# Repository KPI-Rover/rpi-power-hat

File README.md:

# RPI Power HAT

**In development! Not verified!**

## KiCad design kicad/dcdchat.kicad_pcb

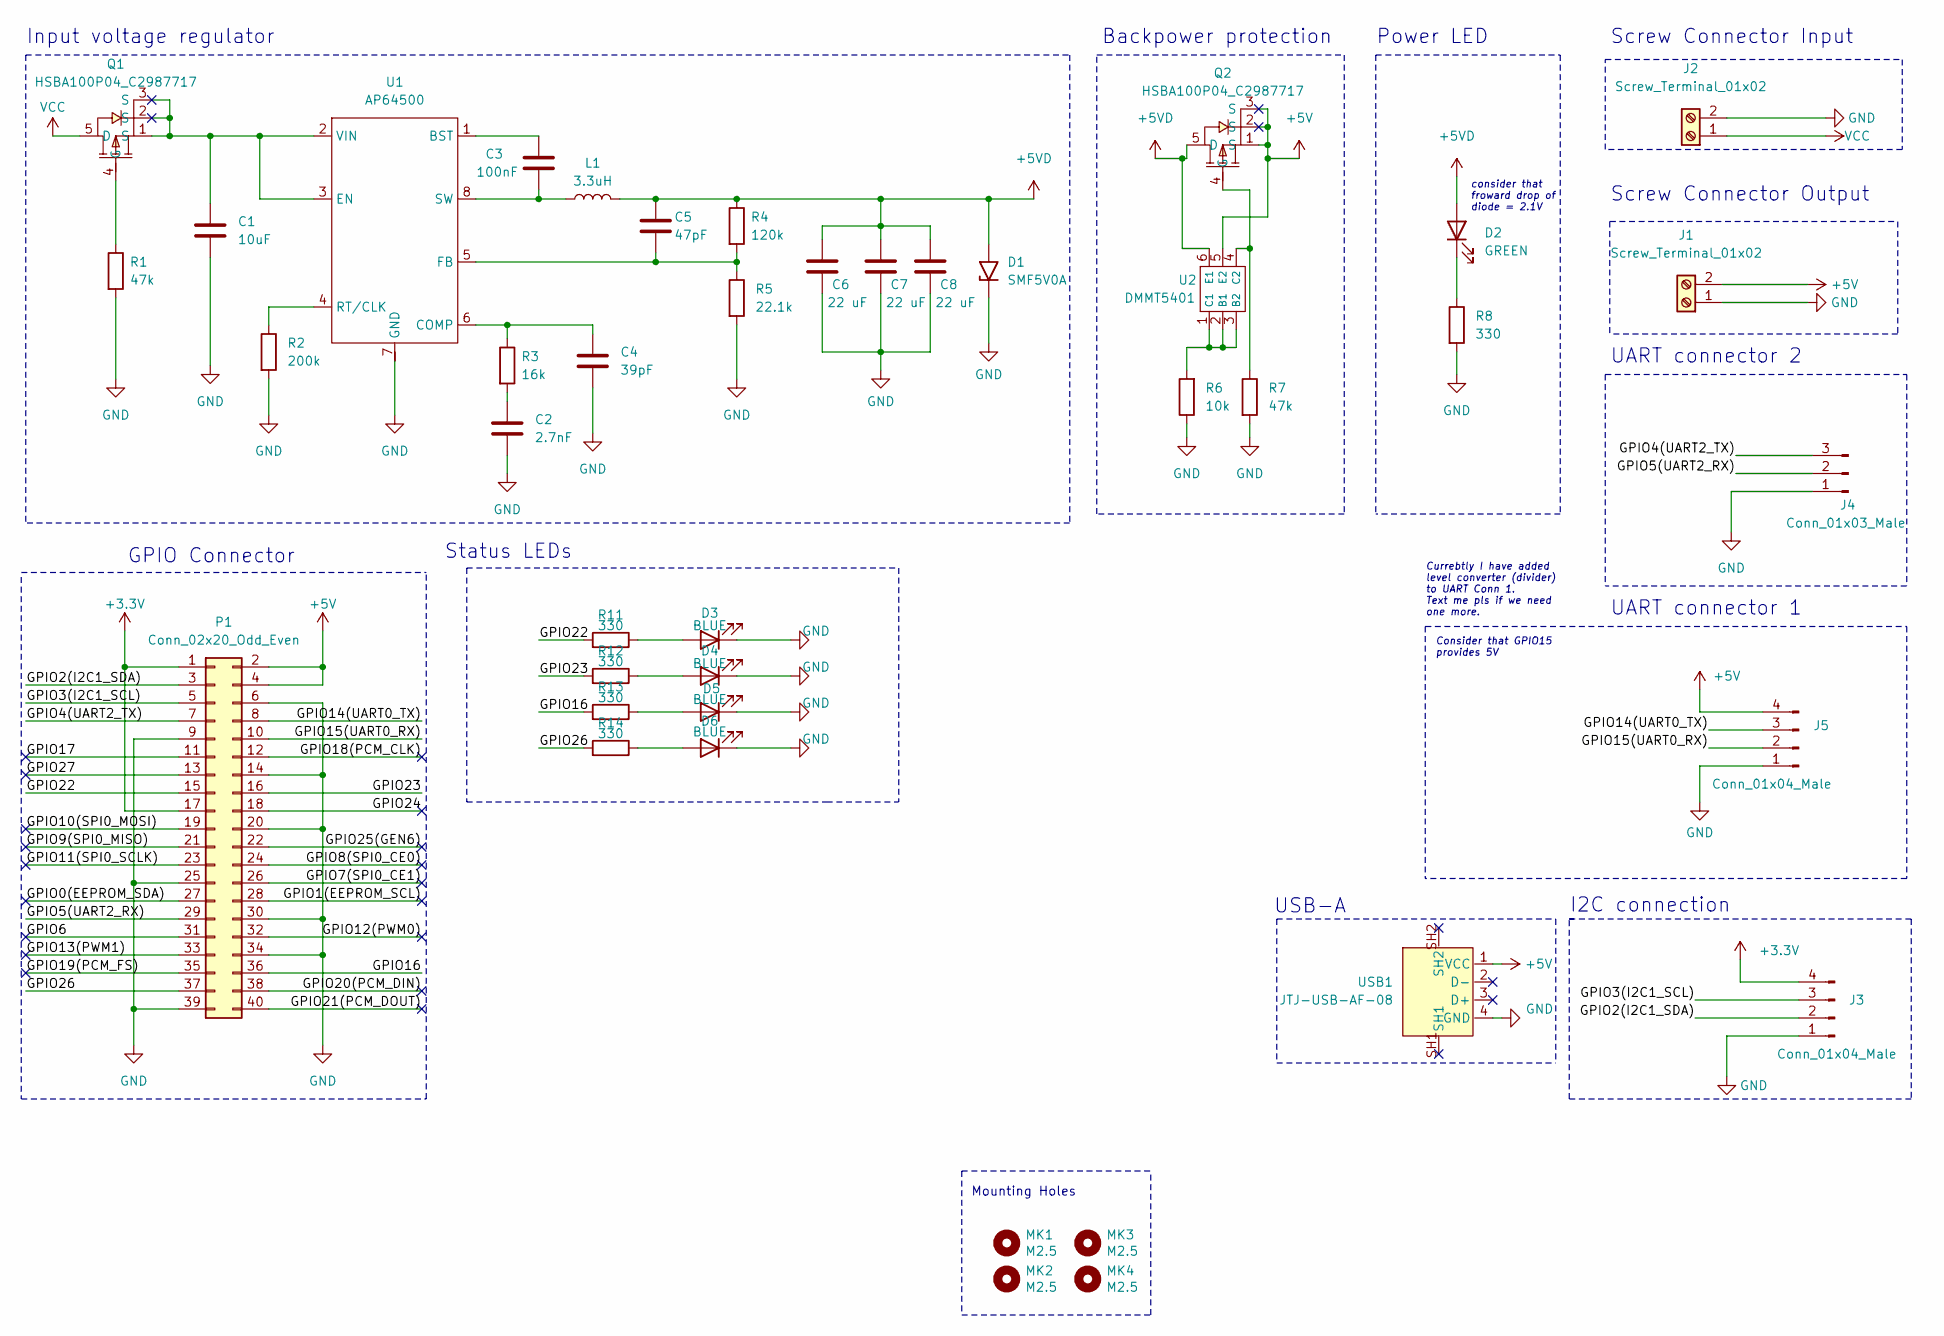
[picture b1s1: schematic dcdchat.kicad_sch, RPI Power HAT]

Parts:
C1: 10uF; C_1206_3216Metric; LCSC C13585
C2: 2.7nF; C_0805_2012Metric; LCSC C2918070
C3: 100nF; C_0805_2012Metric; LCSC C28233
C4: 39pF; C_0805_2012Metric; LCSC C576897
C5: 47pF; C_0805_2012Metric; LCSC C113821
C6, C7, C8: 22 uF; C_1206_3216Metric; LCSC C87996
D1: SMF5V0A; D_SMF; LCSC C42387343
D2: GREEN; LED_0805_2012Metric; LCSC C5875740
D3, D4, D5, D6: BLUE; LED_0805_2012Metric; LCSC C965817
J1, J2: Screw_Terminal_01x02; CONN-TH_2P-P5.08; LCSC C3018698
J3, J5: Conn_01x04_Male; JST_PH_B4B-PH-K_1x04_P2.00mm_Vertical; LCSC C131334
J4: Conn_01x03_Male; JST_PH_B3B-PH-K_1x03_P2.00mm_Vertical; LCSC C131339
L1: 3.3uH; IND-SMD_L11.6-W10.1; LCSC C7587741
MK1, MK2, MK3, MK4: M2.5; MountingHole_2.7mm_M2.5_Pad
P1: Conn_02x20_Odd_Even; PinSocket_2x20_P2.54mm_Vertical; Manufacturer_Part_Number C50982; LCSC C50982
Q1, Q2: HSBA100P04_C2987717; DFN-8_L5.7-W5.1-P1.27-LS6.1-BL-1; LCSC Part C2987717
R1, R7: 47k; R_0805_2012Metric; LCSC C2989281
R2: 200k; R_0805_2012Metric; LCSC C728645
R3: 16k; R_0805_2012Metric; LCSC C865809
R4: 120k; R_0805_2012Metric; LCSC C103948
R5: 22.1k; R_0805_2012Metric; LCSC C2692772
R6: 10k; R_0805_2012Metric; LCSC C110775
R8, R11, R12, R13, R14: 330; R_0805_2012Metric; LCSC C2989109
U1: AP64500; AP64500SP-13; LCSC C2070920
U2: DMMT5401; SOT-23-6; LCSC C154733
USB1: JTJ-USB-AF-08; USB-A-TH__USB-AF-90; LCSC Part C2345

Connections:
+3.3V: J3.4, P1.1, P1.17
+5V: J1.2, J5.4, P1.2, P1.4, Q2.1 (S), Q2.2 (S), Q2.3 (S), U2.5 (E2), USB1.1 (VCC)
+5VD: C5.1, C6.1, C7.1, C8.1, D1.2 (A2), D2.2 (A), L1.2, Q2.5 (D), R4.1, U2.6 (E1)
/GPIO0(EEPROM_SDA): P1.27
/GPIO1(EEPROM_SCL): P1.28
/GPIO2(I2C1_SDA): J3.2, P1.3
/GPIO3(I2C1_SCL): J3.3, P1.5
/GPIO4(UART2_TX): J4.3, P1.7
/GPIO5(UART2_RX): J4.2, P1.29
/GPIO6: P1.31
/GPIO7(SPI0_CE1): P1.26
/GPIO8(SPI0_CE0): P1.24
/GPIO9(SPI0_MISO): P1.21
/GPIO10(SPI0_MOSI): P1.19
/GPIO11(SPI0_SCLK): P1.23
/GPIO12(PWM0): P1.32
/GPIO13(PWM1): P1.33
/GPIO14(UART0_TX): J5.3, P1.8
/GPIO15(UART0_RX): J5.2, P1.10
/GPIO16: P1.36, R13.2
/GPIO17: P1.11
/GPIO18(PCM_CLK): P1.12
/GPIO19(PCM_FS): P1.35
/GPIO20(PCM_DIN): P1.38
/GPIO21(PCM_DOUT): P1.40
/GPIO22: P1.15, R11.2
/GPIO23: P1.16, R12.2
/GPIO24: P1.18
/GPIO25(GEN6): P1.22
/GPIO26: P1.37, R14.2
/GPIO27: P1.13
GND: C1.2, C2.2, C4.2, C6.2, C7.2, C8.2, D1.1 (A1), D3.1 (K), D4.1 (K), D5.1 (K), D6.1 (K), J1.1, J2.2, J3.1, J4.1, J5.1, P1.6, P1.9, P1.14, P1.20, P1.25, P1.30, P1.34, P1.39, R1.2, R2.2, R5.2, R6.1, R7.2, R8.2, U1.7 (GND), U1.EPAD, USB1.4 (GND)
unnamed: C2.1, R3.2
unnamed: D2.1 (K), R8.1
unnamed: D3.2 (A), R11.1
unnamed: D4.2 (A), R12.1
unnamed: D5.2 (A), R13.1
unnamed: D6.2 (A), R14.1
unnamed: Q1.4 (G), R1.1
unnamed: Q2.4 (G), R7.1, U2.4 (C2)
unnamed: C3.1, U1.1 (BST)
unnamed: C4.1, R3.1, U1.6 (COMP)
unnamed: C5.2, R4.2, R5.1, U1.5 (FB)
unnamed: R2.1, U1.4 (RT/CLK)
unnamed: C3.2, L1.1, U1.8 (SW)
unnamed: R6.2, U2.1 (C1), U2.2 (B1), U2.3 (B2)
VCC: J2.1, Q1.5 (D)

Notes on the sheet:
USB-A
Currebtly I have added level converter (divider) to UART Conn 1. Text me pls if we need one more.
Backpower protection
Mounting Holes
I2C connection
GPIO Connector
UART connector 2
Status LEDs
Consider that GPIO15 provides 5V
consider that froward drop of diode = 2.1V
Screw Connector Output
Input voltage regulator
UART connector 1
Power LED
Screw Connector Input

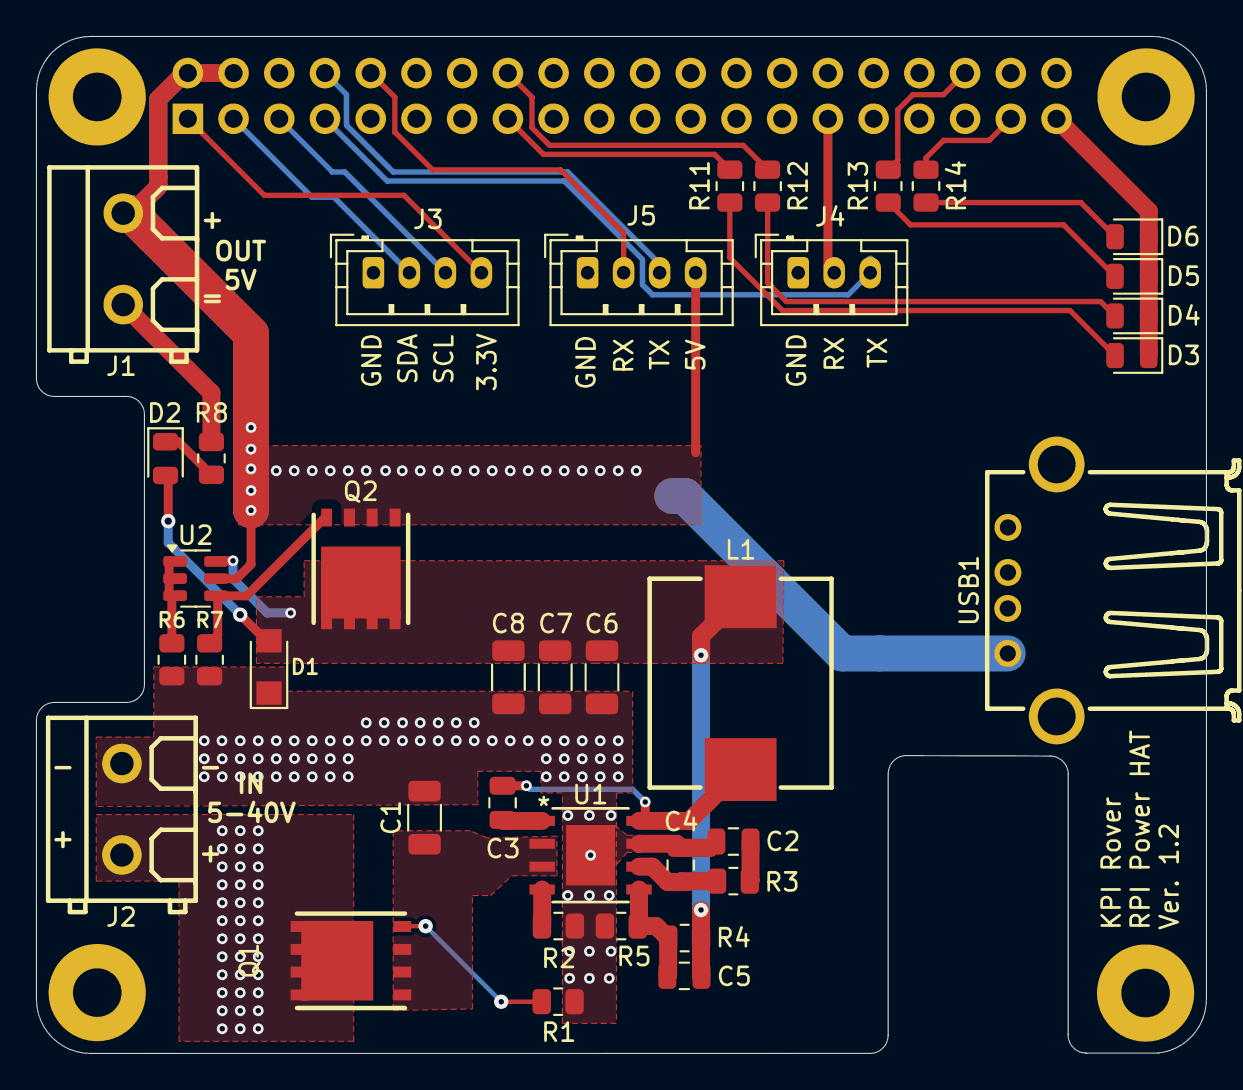
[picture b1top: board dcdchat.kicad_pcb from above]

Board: 2 copper layers, 65.0 x 56.5 mm, 42 parts (1 on the bottom side), 29 nets.

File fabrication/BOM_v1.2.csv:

Reference,Value,Qty,LCSC,LCSC Part
C1,10uF,1,C13585 ,
C2,2.7nF,1,C2918070,
C3,100nF,1,C28233,
C4,39pF,1,C576897,
C5,47pF,1,C113821,
"C6,C7,C8",22 uF,3,C87996,
D1,SMF5V0A,1,C42387343,
D2,GREEN,1,C5875740,
"D3,D4,D5,D6",BLUE,4,C965817,
"J1,J2",Screw_Terminal_01x02,2,C3018698,
"J3,J5",Conn_01x04_Male,2,C131334,
J4,Conn_01x03_Male,1,C131339,
L1,3.3uH,1,C7587741,
"MK1,MK2,MK3,MK4",M2.5,4,,
P1,Conn_02x20_Odd_Even,1,C50982,
"Q1,Q2",HSBA100P04_C2987717,2,C2987717,
"R1,R7",47k,2,C2989281,
R2,200k,1,C728645,
R3,16k,1,C865809,
R4,120k,1,C103948,
R5,22.1k,1,C2692772,
R6,10k,1,C110775,
"R8,R11,R12,R13,R14",330,5,C2989109,
U1,AP64500,1,C2070920,
U2,DMMT5401,1,C154733,
USB1,JTJ-USB-AF-08,1,C2345,

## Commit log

2024-10-20 Move requirements to dedicated document
2024-10-25 Add new requirements
    - Вимоги до розташування компонентів
    - Кріплення
    - Роз'єм для HC-05
2024-11-05 Add reuirements for RPI HAT
2024-11-10 Added input voltage regulator, backpower protection circuit, outer device power relay schematic
2024-11-12 added gpio connector
2024-11-12 Added readme, added CHassis connector
2024-11-17 Fixes in pinout, deleting relay
2024-11-18 Added schematic for connector. Added diode to protect from wrong polarity . Added footprintlibrary for AP64500
2024-11-19 Added TVS-diode
2024-11-25 Added footprints for elements
2024-11-25 fixed 2, 3, 4, 5, 6 in 25.11.2024 message
2024-11-26 fixed 7, 8. Added level converter from 5v to 3.3V
2024-11-26 Added backpower protection diode BSS84 before DC-DC
2024-11-29 made changes due to 28.11.2024 message
2024-12-02 DC-DC converter elements values changes
2024-12-03 Done changes in 2.12.2024 message
2024-12-08 Assigning footprints and placing components in PCB editor
2024-12-10 Replacing components in PCB editor due to 08.12.2024 message
2024-12-15 Added polygons between pins. Havent added polygons for GND and output connection yet
2024-12-29 added traces and polygons on PCB
2025-01-01 Finalize the PCB layout
2025-01-01 Clean Up
2025-03-08 Made improvements to schematic
2025-04-10 Created Improvements_Summary.md
2025-05-15 Final improvements
2025-05-25 Issue #2: Prepare for production
2025-07-01 Issue #4: Made improvements to board
2025-07-01 Issue #4: Update README.md
2025-07-01 Issue #4: Prepare for production

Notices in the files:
parts and their libraries:
Copyright 2016 Accelerated Designs. All rights reserved.
